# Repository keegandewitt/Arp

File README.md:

# prisme - MIDI/CV Translation Hub

A powerful MIDI/CV translation hub built on CircuitPython that bridges the MIDI and modular synthesis worlds with user-configurable layer processing.

```
┌─────────────────────────────┐
│  OLED FeatherWing           │  ← UI + Buttons (STACKED)
├─────────────────────────────┤
│  Feather M4 CAN Express     │  ← Brain (120MHz ARM)
└─────────────────────────────┘
         ↓ USB-C
    [Computer/DAW]

[BREADBOARD]
  MIDI I/O (DIN-5 jacks) ──jumpers──> D0/D1 on M4
  CV/Gate circuits
  Op-amp circuits

⚠️ IMPORTANT: MIDI FeatherWing is NOT stacked - stays on breadboard
```

---

## What It Does

**Concept:** User-definable MIDI/CV processing pipeline with configurable layer ordering

**Input:** MIDI IN (DIN-5), USB MIDI, CV IN (future), Gate IN (future)
**Processing:** Translation layers (Scale Quantization → Arpeggiation, or vice versa)
**Output:** MIDI OUT (DIN-5), USB MIDI, CV/Gate, Custom CC mapping

### Core Features (Working)
- ✅ **Routing Modes:** THRU (zero-latency pass-through) or TRANSLATION (layer processing)
- ✅ **Translation Layers:** Scale quantization, Arpeggiation (user-definable order)
- ✅ **Arpeggiator:** 16 patterns (Up, Down, Up/Down, Random, As-Played, etc.)
- ✅ **Clock System:** Internal/External sync, clock division (16th, 8th, quarter notes)
- ✅ **Custom CC Mapping:** Learn mode for flexible CC output (Session 14)
- ✅ **Settings Persistence:** NVM storage with auto-save
- ✅ **OLED UI:** Real-time display with 3-button navigation

### Translation Hub Features (Planned - Session 15+)
- ⏳ **Layer Ordering:** Scale → Arp OR Arp → Scale (user choice)
- ⏳ **Clock Transformations:** Swing (Roger Linn method), Multiply (2x, 4x), Divide (1/2, 1/4, 1/8)
- ⏳ **Input Selection:** MIDI IN, USB MIDI, CV IN, Gate IN
- ⏳ **CV/Gate Output:** 1V/octave pitch + gate triggers (MCP4728 DAC)
- ⏳ **USB MIDI Notes:** Full USB MIDI input (currently clock only)

### Future Expansions
- 📋 S-Trigger support for vintage gear (ARP, Korg MS, Yamaha CS)
- 📋 Advanced arpeggiator features (latch mode, velocity passthrough)
- 📋 CV IN: Analog voltage input for pitch control

---

## Project Status

**Current Phase:** Translation Hub Architecture - Research Complete ✅ | Implementation Planned ⏳

**Latest:**
- Session 15: Translation Hub architecture research complete (97% confidence)
- Session 14: Custom CC output system implemented and working
- Session 13: CV/Gate output hardware tested and validated
- Core arpeggiator working with 16 patterns, clock sync, settings persistence

See [docs/context/CONTEXT.md](docs/context/CONTEXT.md) for detailed session history and [docs/implementation/TRANSLATION_HUB_IMPLEMENTATION_PLAN.md](docs/implementation/TRANSLATION_HUB_IMPLEMENTATION_PLAN.md) for next steps.

---

## Documentation

### Overview
- **[ARCHITECTURE.md](docs/ARCHITECTURE.md)** - Complete system design
- **[PROJECT_STATUS.md](docs/PROJECT_STATUS.md)** - Current progress and next steps
- **[METHODOLOGY.md](docs/METHODOLOGY.md)** - Development approach

### Hardware
- **[ASSEMBLY_PROTOCOL.md](docs/hardware/ASSEMBLY_PROTOCOL.md)** - Step-by-step build guide
- **[MIDI_PREFLIGHT_CHECKLIST.md](docs/hardware/MIDI_PREFLIGHT_CHECKLIST.md)** - Pre-flight validation
- **[MIDI_BREADBOARD_WIRING.md](docs/hardware/MIDI_BREADBOARD_WIRING.md)** - Breadboard testing guide

### Software
- **[UI_ARCHITECTURE.md](docs/UI_ARCHITECTURE.md)** - Button interaction standards

---

## Hardware

### Bill of Materials
- [Adafruit Feather M4 CAN Express](https://www.adafruit.com/product/4759) - Main board
- [Adafruit MIDI FeatherWing](https://www.adafruit.com/product/4740) - MIDI IN/OUT
- [Adafruit OLED FeatherWing 128x64](https://www.adafruit.com/product/4650) - Display + 3 buttons
- USB-C cable
- MIDI cables (DIN-5)

**Future (Phase 2):**
- 3x 3.5mm mono jacks (CV, Gate, Velocity)
- Op-amp circuit (for 1V/octave scaling)

### Pin Usage

**Currently Used:**
```
D0, D1     → MIDI FeatherWing (UART)
D5, D6, D9 → OLED Buttons
D21, D22   → OLED Display (I2C)
```

**Reserved for Future:**
```
A0  → CV Pitch Out (DAC)
A1  → CV Velocity Out (DAC)
A2  → Gate/Trigger Out
A3  → S-Trigger Out
```

See [ARCHITECTURE.md - Pin Allocation](docs/ARCHITECTURE.md#pin-allocation) for complete details.

---

## Software Architecture

### Modular Design
```
[MIDI Input] → [Arpeggiator Engine] → [Output Router]
                                           ↓
                                  ┌────────┼────────┐
                                  ↓        ↓        ↓
                               MIDI    CV/Gate  S-Trig
                              Driver   Driver   Driver
```

### Directory Structure
```
/
├── main.py                      # Main entry point (current inline arpeggiator)
├── arp/
│   ├── core/
│   │   ├── arpeggiator.py       # Class-based arpeggiator (16 patterns, scale quantization)
│   │   ├── clock.py             # Clock handler (internal/external sync)
│   │   ├── config.py            # Settings with NVM persistence
│   │   ├── custom_cc.py         # Custom CC mapping with Learn Mode (Session 14)
│   │   └── cv_gate.py           # CV/Gate output driver (MCP4728)
│   ├── ui/
│   │   ├── display.py           # OLED display manager (SH1107)
│   │   ├── menu.py              # Menu system
│   │   └── buttons.py           # Button handler
│   └── lib/                     # CircuitPython libraries
├── docs/
│   ├── context/                 # Session handoffs and project context
│   ├── implementation/          # Implementation plans and research
│   ├── hardware/                # Hardware documentation, tests, schematics
│   └── ARCHITECTURE.md          # System architecture
└── tests/                       # Hardware validation and unit tests
```

### Dependencies
- CircuitPython 10.0.3
- `adafruit_displayio_sh1107` - OLED driver
- `adafruit_midi` - MIDI protocol
- `i2cdisplaybus` - I2C management

---

## Development

### Setup
1. Install CircuitPython 10.0.3 on Feather M4
2. Install libraries:
   ```bash
   circup install adafruit_displayio_sh1107 adafruit_midi
   ```
3. Clone repository:
   ```bash
   git clone https://github.com/keegandewitt/prisme.git prisme
   cd prisme
   ```

### Testing
Use the comprehensive test suite:
```bash
# MIDI tests
python3 scripts/monitor_serial.py --reload &
cp tests/midi_loopback_test.py /Volumes/CIRCUITPY/code.py

# Integration test
cp tests/integration_test_debug.py /Volumes/CIRCUITPY/code.py
```

See [tests/](tests/) directory for all test scripts.

### Serial Monitoring
Clean serial port monitoring with automatic cleanup:
```bash
python3 scripts/monitor_serial.py --reload --duration 60
```

---

## Features

### Translation Hub Architecture
- **Routing Modes:** THRU (zero-latency) or TRANSLATION (layer processing)
- **Layer Ordering:** User-configurable (Scale → Arp OR Arp → Scale)
- **Layer Enable/Disable:** Independent control of each translation layer

### Arpeggiator Engine (16 Patterns)
- **Up:** Ascending notes
- **Down:** Descending notes
- **Up/Down:** Ascending then descending (palindrome)
- **Down/Up:** Descending then ascending
- **Random:** Random note selection
- **As-Played:** Remembers input order
- **+ 10 more patterns** in class-based arpeggiator

### Scale Quantization
- **Scales:** Major, Minor, Dorian, Phrygian, Lydian, Mixolydian, Aeolian, Locrian
- **Root Note:** Chromatic selection (C through B)
- **Real-time quantization:** Notes snap to scale during performance

### Clock System
- **Sources:** USB MIDI Clock, DIN MIDI Clock, Internal (free-running)
- **Divisions:** 16th notes, 8th notes, Quarter notes
- **Transformations (Planned):** Swing (50-75%), Multiply (2x, 4x), Divide (1/2, 1/4, 1/8)

### Custom CC Mapping (Session 14)
- **Learn Mode:** Button B long press to capture CC assignments
- **Smoothing:** Configurable smoothing for jitter reduction
- **Flexible Routing:** Map any input CC to any output CC

### UI Controls
**Single Press:**
- Button A: Navigate menu / Cycle pattern
- Button B: Navigate menu / Cycle clock division
- Button C: Navigate menu / Select option

**Long Press (0.5s):**
- Button A: Enter/exit menu system
- Button B: **Learn Mode** (Custom CC mapping)
- Button C: Context-specific action

---

## Performance

- **MIDI Latency:** <5ms (input to output)
- **Clock Jitter:** <1ms
- **Loop Rate:** 100Hz (10ms)
- **Display Update:** 30Hz (33ms)
- **Stability:** 25+ minutes validated

---

## Repository

- **GitHub:** https://github.com/keegandewitt/prisme
- **License:** MIT (TBD)
- **Issues:** [Report bugs](https://github.com/keegandewitt/prisme/issues)

---

## Resources

### Datasheets
- [Feather M4 CAN](https://learn.adafruit.com/adafruit-feather-m4-can-express)
- [MIDI FeatherWing](https://learn.adafruit.com/adafruit-midi-featherwing)
- [OLED FeatherWing](https://learn.adafruit.com/adafruit-128x64-oled-featherwing)

### CircuitPython
- [CircuitPython Docs](https://docs.circuitpython.org/)
- [CircuitPython MIDI Guide](https://learn.adafruit.com/circuitpython-midi-projects)

### Standards
- [MIDI 1.0 Specification](https://www.midi.org/specifications)
- [CV/Gate Standards](https://en.wikipedia.org/wiki/CV/gate)

---

## Development Philosophy

> **"Measure twice, cut once"**

This project emphasizes:
1. ✅ **Thorough planning** before implementation
2. ✅ **Hardware validation** before software development
3. ✅ **Comprehensive testing** at each stage
4. ✅ **Clear documentation** for maintainability
5. ✅ **Modular architecture** for future expansion

See [METHODOLOGY.md](docs/METHODOLOGY.md) for our development approach.

---

## Roadmap

### Completed (Sessions 1-14)
- ✅ Arpeggiator engine core (16 patterns)
- ✅ Clock synchronization (USB/DIN/Internal)
- ✅ UI menu system (7 categories)
- ✅ Settings persistence (NVM storage)
- ✅ Custom CC mapping with Learn Mode
- ✅ CV/Gate output driver (MCP4728 DAC)
- ✅ OLED display integration (SH1107)

### Current Focus (Session 15)
- ⏳ Translation Hub architecture research (97% complete)
- ⏳ Implementation plan finalized
- ⏳ Documentation updates to reflect "prisme" rebranding

### Next Session (Session 16+)
- 📋 Migrate to class-based arpeggiator architecture
- 📋 Implement translation layer pipeline
- 📋 Add swing/multiply/divide to clock system
- 📋 Enable USB MIDI for note input (currently clock only)
- 📋 Implement configurable layer ordering (Scale→Arp or Arp→Scale)
- 📋 Add routing mode selection (THRU / TRANSLATION)
- 📋 Comprehensive testing (PyTest + hardware validation)

### Long Term
- 📋 Input source selection (CV IN, Gate IN)
- 📋 S-Trigger support for vintage gear
- 📋 Advanced arpeggiator features (latch, velocity curves)

---

## Contributing

This is currently a personal project, but contributions and suggestions are welcome!

1. Check [PROJECT_STATUS.md](docs/PROJECT_STATUS.md) for current work
2. Review [ARCHITECTURE.md](docs/ARCHITECTURE.md) for system design
3. Open an issue to discuss your ideas

---

## Acknowledgments

- **Adafruit** - Amazing hardware and CircuitPython
- **CircuitPython Community** - Excellent documentation and libraries

---

**Project:** prisme - MIDI/CV Translation Hub
**Version:** 3.0 (Translation Hub Architecture)
**Status:** Core features working, Translation Hub implementation planned
**Last Updated:** 2025-11-01 (Session 15)

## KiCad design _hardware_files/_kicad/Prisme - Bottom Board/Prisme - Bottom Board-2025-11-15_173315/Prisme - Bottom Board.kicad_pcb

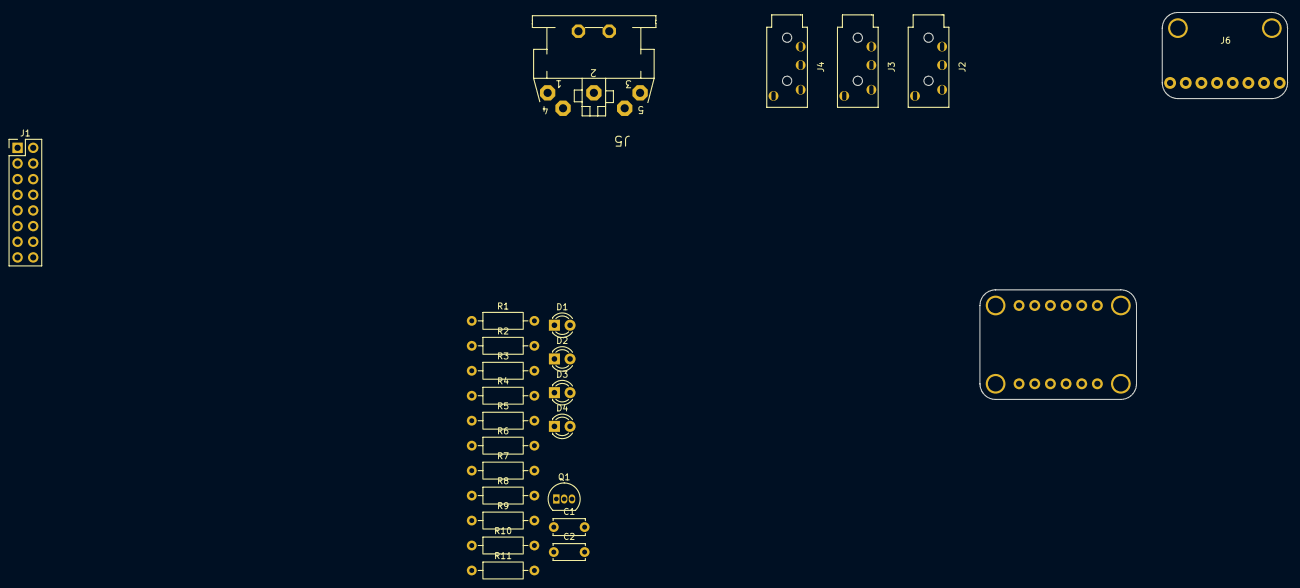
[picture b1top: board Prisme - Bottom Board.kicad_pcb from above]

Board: 2 copper layers, 25 parts (0 on the bottom side), 24 nets, no tracks yet.

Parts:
C1, C2: 100pF; C_Disc_D5.0mm_W2.5mm_P5.00mm
D1, D2, D3, D4: LED; LED_D3.0mm_FlatTop
J1: Conn_02x08_Odd_Even; PinHeader_2x08_P2.54mm_Vertical
J2, J3, J4: PJ-320A
J5: 1134; 1134_footprint
J6: Adafruit_USB-C_4090; Adafruit_4090_USBCBreakout
Q1: PNP; TO-92_Inline
R1, R2, R3, R11: 100Ω; R_Axial_DIN0207_L6.3mm_D2.5mm_P10.16mm_Horizontal
R4, R5, R6, R7, R8, R9: 220Ω; R_Axial_DIN0207_L6.3mm_D2.5mm_P10.16mm_Horizontal
R10: 1kΩ; R_Axial_DIN0207_L6.3mm_D2.5mm_P10.16mm_Horizontal
U1: MCP4728; AdaFruit_MCP4728

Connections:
+3.3v: C1.1, C1.2, J1.3, R4.1
+5v: J1.1, J6.2 (VBUS), Q1.3 (E), U1.1 (VCC)
CCOUT: R3.2, U1.10 (VC)
CCOUTLED: J1.8, R8.2
CVOUT: R2.2, U1.8 (VA)
CVOUTLED: J1.6, R6.2
GND: C2.1, D1.1 (K), D2.1 (K), D3.1 (K), D4.1 (K), J1.2, J1.4, J1.15, J2.1 (GND), J3.1 (GND), J4.1 (GND), J6.1 (GND), U1.2 (GND)
MIDIOUT: J1.9, R5.2
MIDIOUTLED: J1.12, R9.2
unnamed: C2.2, J5.2
unnamed: D1.2 (A), R6.1
unnamed: D2.2 (A), R7.1
unnamed: D3.2 (A), R8.1
unnamed: D4.2 (A), R9.1
unnamed: J2.2, R1.1
unnamed: J3.2, R2.1
unnamed: J4.2, R3.1
unnamed: J5.4, R4.2
unnamed: J5.5, R5.1
SCL: J1.7, U1.3 (SCL)
SDA: J1.5, U1.4 (SDA)
STRIGOUT: J1.11, R10.2
TRIGOUT: R1.2, R11.1, U1.9 (VB)
TRIGOUTLED: J1.10, R7.2

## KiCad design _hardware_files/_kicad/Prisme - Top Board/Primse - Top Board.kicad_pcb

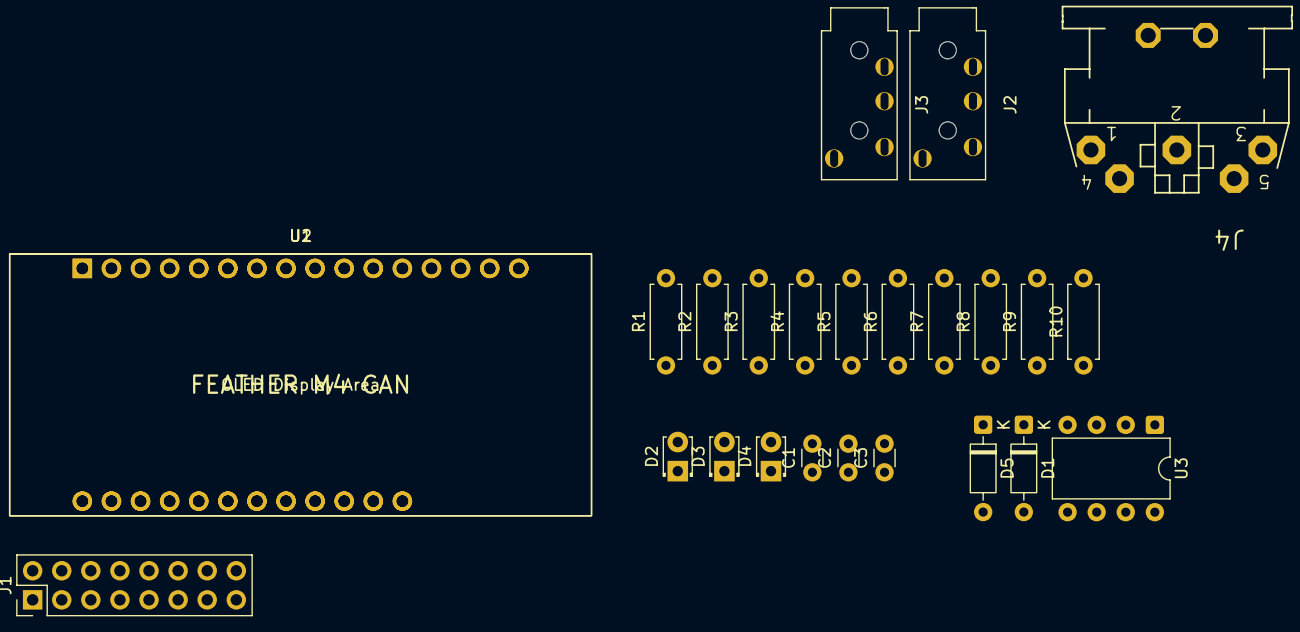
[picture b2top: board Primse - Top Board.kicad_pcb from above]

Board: 2 copper layers, 25 parts (0 on the bottom side), 28 nets, no tracks yet.

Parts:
C1, C2, C3: 100nF; C_Disc_D3.0mm_W1.6mm_P2.50mm
D1, D5: BAT85; D_DO-35_SOD27_P7.62mm_Horizontal
D2, D3, D4: LED; LED_D1.8mm_W3.3mm_H2.4mm
J1: Conn_02x08_Odd_Even; PinHeader_2x08_P2.54mm_Vertical
J2, J3: PJ-320A
J4: 1134; 1134_footprint
R1, R3: 20kΩ; R_Axial_DIN0207_L6.3mm_D2.5mm_P7.62mm_Horizontal
R2, R4: 22kΩ; R_Axial_DIN0207_L6.3mm_D2.5mm_P7.62mm_Horizontal
R5, R10: 1k; R_Axial_DIN0207_L6.3mm_D2.5mm_P7.62mm_Horizontal
R6, R7, R8, R9: 220Ω; R_Axial_DIN0207_L6.3mm_D2.5mm_P7.62mm_Horizontal
U1: Adafruit_Feather_M4_CAN
U2: Adafruit_OLED_FeatherWing
U3: 6N138; DIP-8_W7.62mm

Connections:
+3.3V: C3.1, D1.2 (A), J1.3, R10.2, U1.2 (3V3), U2.2 (3V3)
+5V: J1.1, U1.19 (VUSB)
CCOUTLED: J1.8, U1.6 (A1)
CVIN: C1.2, D1.1 (K), R1.2, R2.1, U1.8 (A3)
CVINLED: R7.2, U1.16 (D4)
CVOUTLED: J1.6, U1.21 (D12)
GND: C1.1, C2.1, C3.2, D2.1 (K), D3.1 (K), D4.1 (K), J1.2, J1.4, J1.15, J2.1 (GND), J3.1 (GND), J4.2, R2.2, R4.2, U1.4 (GND), U2.4 (GND), U3.5 (GND), U3.8 (VCC)
MIDIIN: U1.14 (RX), U3.6 (VO2)
MIDIINLED: R9.2, U1.7 (A2)
MIDIOUT: J1.9, U1.15 (TX)
MIDIOUTLED: J1.12, U1.10 (A5)
unnamed: D2.2 (A), R7.1
unnamed: D3.2 (A), R8.1
unnamed: D4.2 (A), R9.1
unnamed: D5.2 (A), R5.1
unnamed: D5.1 (K), J4.4
unnamed: J2.2, R1.1
unnamed: J3.2, R3.1
unnamed: J4.5, R6.1
unnamed: R6.2, U3.2 (C1)
unnamed: R5.2, U3.3 (C2)
unnamed: R10.1, U3.7 (VO1)
SCL: J1.7, U1.27 (SCL), U2.27 (SCL)
SDA: J1.5, U1.28 (SDA), U2.28 (SDA)
STRIGOUT: J1.11, U1.23 (D10)
TRIGIN: C2.2, R3.2, R4.1, U1.9 (A4)
TRIGINLED: R8.2, U1.22 (D11)
TRIGOUTLED: J1.10, U1.5 (A0)

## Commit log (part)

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2025-10-22 docs: Add comprehensive handoff for OLED troubleshooting
2025-10-23 docs: Create session handoff system with START_HERE and CONTEXT docs
    - Add START_HERE.md for 30-second onboarding
    - Add docs/context/CONTEXT.md for living session context
    - Add docs/context/SESSION_HANDOFF_METHODOLOGY.md for handoff protocol
    - Update /start and /handoff commands to use Arp project (not Phil)
    - Establishes systematic context preservation between Claude sessions
2025-10-23 docs: Create session handoff system with START_HERE and CONTEXT docs
    - Add START_HERE.md for 30-second onboarding
    - Add docs/context/CONTEXT.md for living session context
    - Add docs/context/SESSION_HANDOFF_METHODOLOGY.md for handoff protocol
    - Update /start and /handoff commands to use Arp project (not Phil)
    - Establishes systematic context preservation between assistant sessions
2025-10-23 feat: Add VintageCapture VST project with working duration analyzer
    - Create project structure (Source/, Resources/, Builds/)
    - Implement DurationAnalyzer for attack/release time detection
    - RMS envelope calculation with 10ms sliding window
    - Attack detection (0-90% of peak)
    - Release detection (note-off to 10% of peak)
    - Build test harness with 3 realistic test cases
2025-10-23 feat: Complete VintageCapture VST plugin implementation
    MAJOR MILESTONE: Full VST plugin for vintage synth capture workflow
    Core Components:
    - KeystrokeCapture: MIDI performance recording with timing
    - MonitoringEngine: Zero-latency sample playback with pitch shifting
    - PluginProcessor: Main VST audio/MIDI engine with state machine
    - PluginEditor: GUI for 3-stage workflow (calibrate/record/playback)
2025-10-23 docs: Update session handoff (Session 5 complete - VintageCapture VST)
2025-10-23 chore: Clean up project - archive old files, add build ignores
    - Archive README.md.old to _archive/
    - Remove VintageCapture/analyzer_test build artifact
    - Update .gitignore for C++ build artifacts (.o, .a, .dylib, .vst3, etc.)
    - Add .gitkeep files for Builds/ and Resources/ directories
    - Add VintageCapture section to main README
    - Optimize project structure for clean repository
2025-10-23 docs: Update CONTEXT.md with latest commit info
2025-10-23 docs: Update CONTEXT.md with /start command commit
2025-10-23 fix: Apply CircuitPython mastery fixes and resolve import error
    - Fix incorrect import in clock.py (midi_continue vs continue_)
    - Move gc and random imports to module level (prevent allocations)
    - Add periodic garbage collection (every 100ms)
    - Pre-allocate DEMO_CHORD constant (save 84 bytes per button press)
    - Consolidate UART pass-through error handling
    - Add optional DEBUG_MEMORY flag for monitoring
2025-10-23 docs: Add VintageCapture VST to PROJECT_STATUS.md
    - Added VintageCapture to Quick Reference table (VST & Vintage Mode)
    - Added Vintage Synth Integration section to Planned Features
    - Added VintageCapture milestone to Recent Milestones (2025-10-23)
    - Added VintageCapture/ directory to File Structure
    - Documents two-stage workflow for vintage synth compatibility
    - References VintageCapture/*.md files for details
2025-10-23 docs: Add VintageCapture VST to PROJECT_STATUS.md
    - Added VintageCapture to Quick Reference table (VST & Vintage Mode)
    - Added Vintage Synth Integration section to Planned Features
    - Added VintageCapture milestone to Recent Milestones (2025-10-23)
    - Added VintageCapture/ directory to File Structure
    - Documents two-stage workflow for vintage synth compatibility
    - References VintageCapture/*.md files for details
2025-10-23 docs: Add comprehensive latency compensation specification
    - Created LATENCY_COMPENSATION.md with complete technical details
    - Added CC 104 (Calibrate Latency) to ARP_FIRMWARE_SPEC.md
    - Added SysEx response format for calibration acknowledgment
    - Includes implementation examples for VST (C++/JUCE) and Arp (CircuitPython)
    - Documents one-button calibration workflow
    - Covers accuracy, limitations, and troubleshooting
2025-10-23 docs: Add comprehensive connector & bus occupancy reference
    - Added detailed JST SH (STEMMA QT) connector tracking
    - Added I2C bus occupancy (OLED + MCP4728 DAC)
    - Added UART, GPIO, Analog/DAC pin status tables
    - Added power rail allocation and current budgets
    - Added MCP4728 DAC channel assignments
    - Added physical output jack mapping
2025-10-23 docs: Create comprehensive System Occupancy Reference
    New holistic occupancy tracking document covering:
    1. Physical Hardware Occupancy
    - Connector occupancy (JST SH / STEMMA QT)
    - I2C bus occupancy
    - UART pin occupancy
    - GPIO pin occupancy
2025-10-23 fix: Resolve button unpacking error and add battery integration docs
    - Fix ValueError in main.py line 324 (missing ac_long parameter)
    - Add comprehensive battery + MCP4728 integration guide
    - Add MCP4728 power setup documentation with safety procedures
    - Update METHODOLOGY.md with verify-then-act protocol
    - Add deployment automation script
    - Install adafruit_mcp4728 library for CV/Gate output
2025-10-24 docs: Document powerboost configuration and voltage level shifter requirements
2025-10-24 docs: Update CONTEXT.md with voltage level requirements and next steps
2025-10-24 feat: Add firmware version reporting and update infrastructure
    - Add version metadata to main.py (__version__, __build_date__, __hardware_version__)
    - Update startup display to show firmware version on OLED
    - Update serial console to show version, build date, and hardware version
    - Create firmware bundle script (scripts/create_bundle.sh)
    - Auto-extracts version from main.py
    - Creates .arpfw bundle (zip) with manifest.json
2025-10-24 docs: Add comprehensive production planning roadmap for 200-unit manufacturing
    - Cost analysis: -51/unit (custom PCB) vs -105/unit (Feathers)
    - Total savings: ,800-12,600 for 200 units
    - Recommend RP2040 instead of SAMD51 ( vs -8 per unit)
    - Strategy: Single custom PCB with integrated MIDI circuit
    - Timeline: 18-24 weeks from prototype to production
    - Includes technical implementation, BOM breakdown, risk assessment
2025-10-24 docs: Update CONTEXT.md with Session 9 production planning summary
2025-10-24 docs: Update CONTEXT.md with Session 10 summary
2025-11-01 docs: Update session handoff (Session 14 complete)
2025-11-01 docs: Architecture reframe - "prisme" MIDI/CV Translation Hub
    MAJOR VISION SHIFT: From "arpeggiator" to full MIDI/CV translation hub
    ## What Changed
    - Project renamed from "Arp" to "prisme" (MIDI data passes through
    like light through a prism - transformed)
    - Redefined as MIDI/CV Translation Hub with multiple translation layers
    - Architecture now supports: Input selection → Routing modes →
2025-11-01 docs: Update session handoff (Session 15 complete)
2025-11-02 docs: Add comprehensive output jack wiring guides with RED/WHITE color standard
2025-11-02 docs: Update session handoff (Session 17 - CV wiring started, MCP4728 debugging needed)
2025-11-02 docs: Update session handoff (Session 19 - OLED split-screen bug blocking)
2025-11-04 docs: Add critical rule against blame-shifting to tools + Session 26 handoff
    - CRITICAL RULE: Never claim tool limitations without multi-point verification
    - Must provide: official docs, third-party sources, concrete technical reasons
    - Banned: Blaming schemdraw/tools for assistant's own failures
    - Required: Own failures, document what wasn't figured out
    Session 26 summary:
    - Attempted unified schematic for EasyEDA
2025-11-04 Revert "fix: Correct MCP4728 DAC channel allocation across all documentation"
    This reverts commit 270c88e25484c09485766df622d8ada8d27d6c6f.
2025-11-11 refactor: Remove AI assistant references from documentation
    - Removed .claude/ directory and configuration files
    - Updated all documentation to use generic development terminology
    - Stripped assistant-specific references from methodology and context docs
    - Maintained all technical content and project history
2025-11-12 fix: Remove embedded git repos from Eagle imports
2025-11-12 docs: Add README for libraries folder
